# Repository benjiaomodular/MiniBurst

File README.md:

# MiniBurst
[![CC BY-SA 4.0][cc-by-sa-shield]][cc-by-sa]

## License

This work is licensed under a
[Creative Commons Attribution-ShareAlike 4.0 International License][cc-by-sa].

[![CC BY-SA 4.0][cc-by-sa-image]][cc-by-sa]

[cc-by-sa]: http://creativecommons.org/licenses/by-sa/4.0/
[cc-by-sa-image]: https://licensebuttons.net/l/by-sa/4.0/88x31.png
[cc-by-sa-shield]: https://img.shields.io/badge/License-CC%20BY--SA%204.0-lightgrey.svg

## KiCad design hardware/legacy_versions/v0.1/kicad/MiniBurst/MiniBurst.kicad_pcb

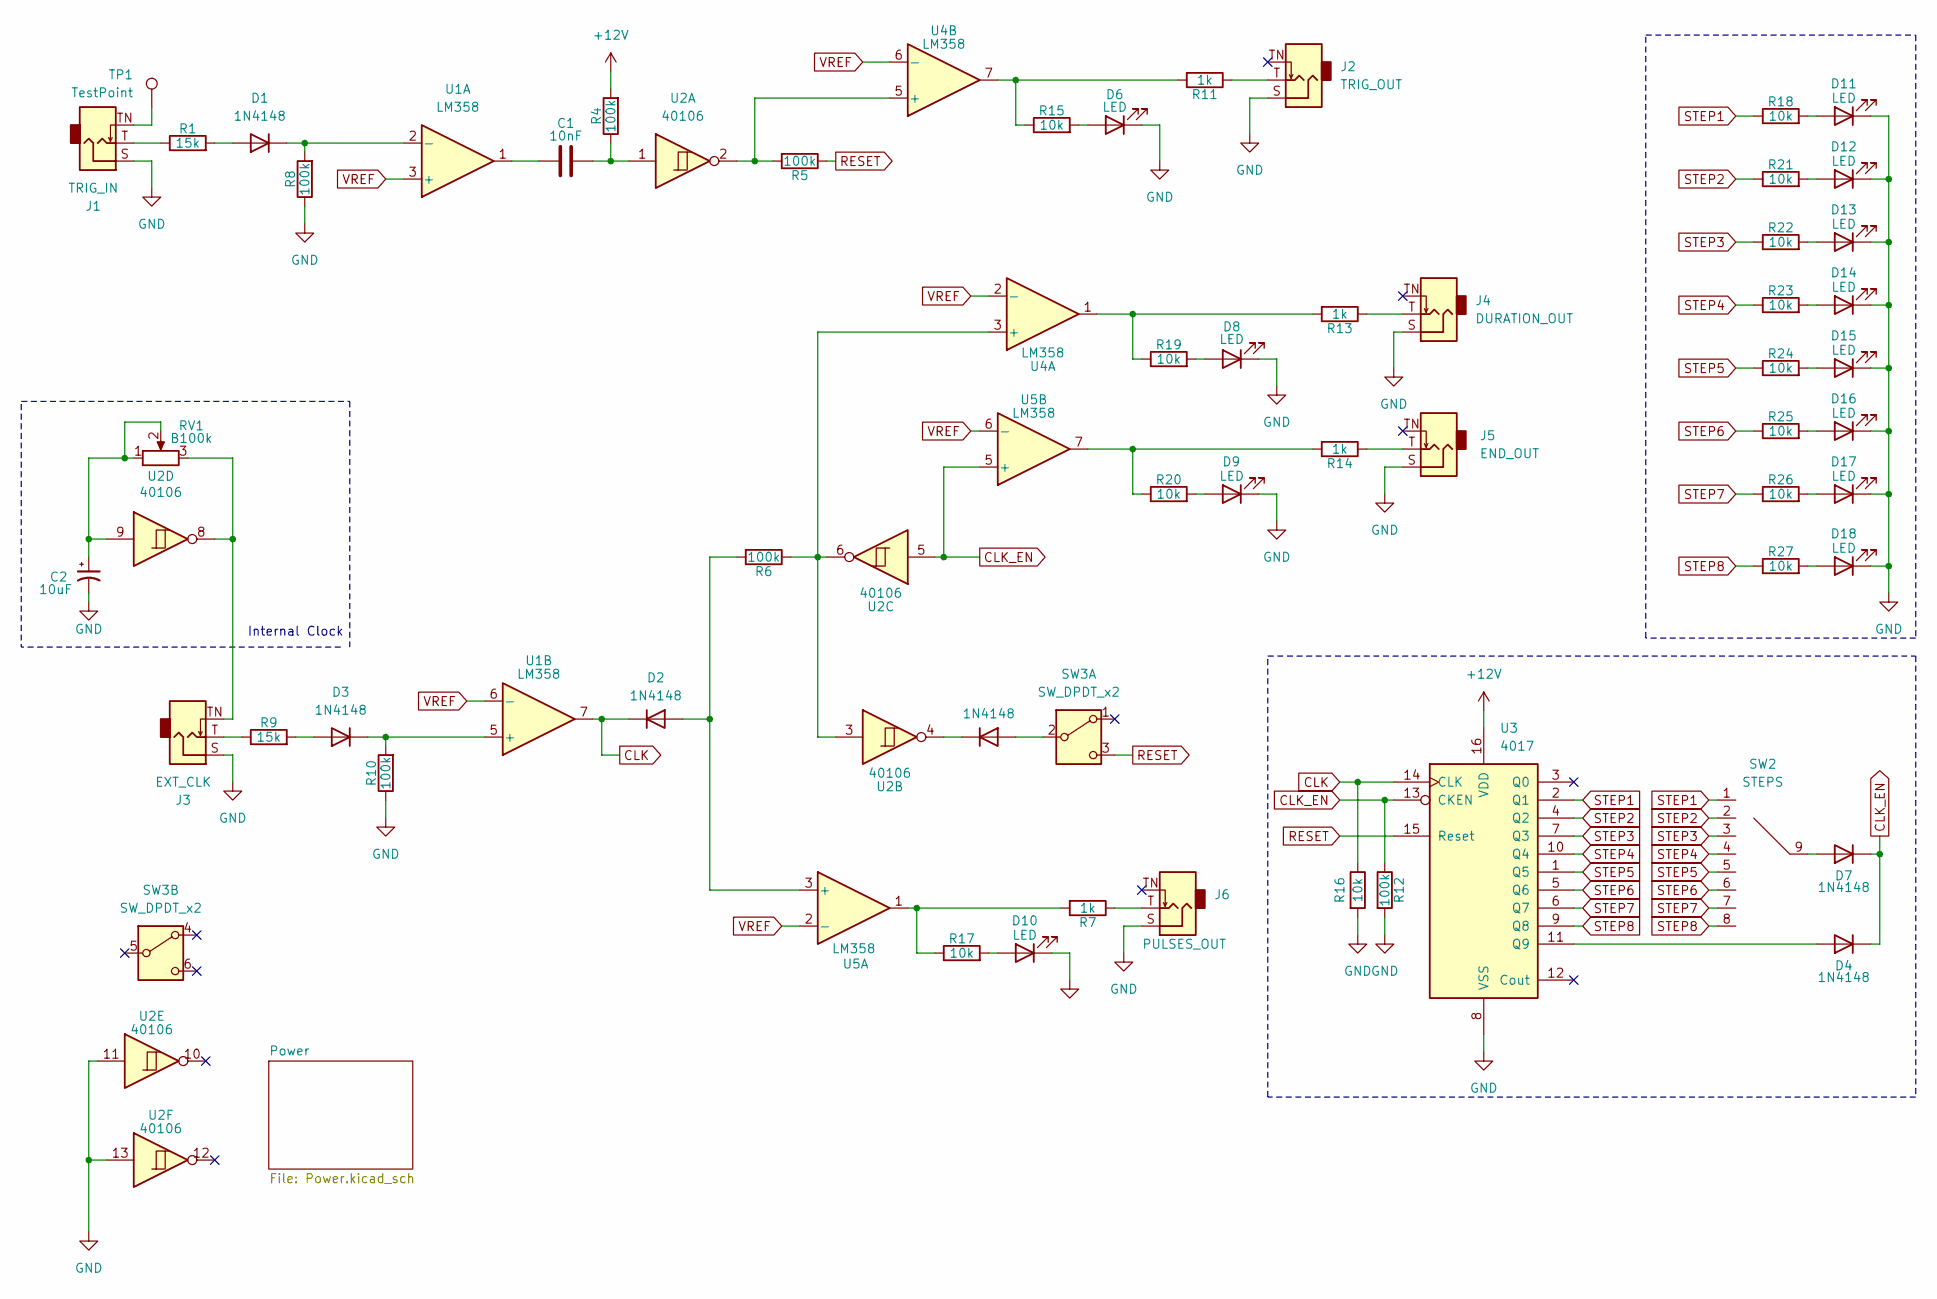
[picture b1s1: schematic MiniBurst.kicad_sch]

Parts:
C1: 10nF; C_0805_2012Metric_Pad1.18x1.45mm_HandSolder
C2: 10uF; C_0805_2012Metric_Pad1.18x1.45mm_HandSolder; Manufacturers Part Numb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 TMK212BBJ106KG8T
D1, D2, D3, D4, D5, D7: 1N4148; D_SOD-123
D6, D8, D9, D10, D11, D12, D13, D14, D15, D16, D17, D18: LED; LED_D3.0mm
J1: TRIG_IN; AudioJack_3.5mm
J2: TRIG_OUT; AudioJack_3.5mm
J3: EXT_CLK; AudioJack_3.5mm
J4: DURATION_OUT; AudioJack_3.5mm
J5: END_OUT; AudioJack_3.5mm
J6: PULSES_OUT; AudioJack_3.5mm
R1, R9: 15k; R_0805_2012Metric
R4, R5, R6, R8, R10, R12: 100k; R_0805_2012Metric
R7, R11, R13, R14: 1k; R_0805_2012Metric
R15, R16, R17, R18, R19, R20, R21, R22, R23, R24, R25, R26, R27: 10k; R_0805_2012Metric
RV1: B100k; Potentiometer_RV09; Manufacturers Part Numb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 RD901F-40-15R1-B100K
SW2: STEPS; RotarySwitch_SR16_POLE1_WAY8
SW3: SW_DPDT_x2; Button_KFC7x7
TP1: TestPoint; SolderWirePad_1x01_SMD_1x2mm
U1, U4, U5: LM358; SOIC-8_3.9x4.9mm_P1.27mm
U2: 40106; SOIC-14_3.9x8.7mm_P1.27mm
U3: 4017; SOIC-16_3.9x9.9mm_P1.27mm

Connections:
+12V: R4.2, U3.16 (VDD); also elsewhere on the board
CLK: D2.1 (K), R16.1, U1.7, U3.14 (CLK)
CLK_EN: D4.1 (K), D7.1 (K), R12.1, U2.5, U3.13 (CKEN), U5.5 (+)
GND: C2.2, D6.1 (K), D8.1 (K), D9.1 (K), D10.1 (K), D11.1 (K), D12.1 (K), D13.1 (K), D14.1 (K), D15.1 (K), D16.1 (K), D17.1 (K), D18.1 (K), J1.S, J2.S, J3.S, J4.S, J5.S, J6.S, R8.1, R10.1, R12.2, R16.2, U2.11, U2.13, U3.8 (VSS); also elsewhere on the board
unnamed: C1.1, U1.1
unnamed: C1.2, R4.1, U2.1
unnamed: C2.1, RV1.1, RV1.2, U2.9
unnamed: D1.2 (A), R1.2
unnamed: D1.1 (K), R8.2, U1.2 (-)
unnamed: D2.2 (A), R6.2, U5.3 (+)
unnamed: D3.2 (A), R9.2
unnamed: D3.1 (K), R10.2, U1.5 (+)
unnamed: D4.2 (A), U3.11 (Q9)
unnamed: D5.2 (A), SW3.2 (B)
unnamed: D5.1 (K), U2.4
unnamed: D6.2 (A), R15.2
unnamed: D7.2 (A), SW2.9
unnamed: D8.2 (A), R19.2
unnamed: D9.2 (A), R20.2
unnamed: D10.2 (A), R17.2
unnamed: D11.2 (A), R18.2
unnamed: D12.2 (A), R21.2
unnamed: D13.2 (A), R22.2
unnamed: D14.2 (A), R23.2
unnamed: D15.2 (A), R24.2
unnamed: D16.2 (A), R25.2
unnamed: D17.2 (A), R26.2
unnamed: D18.2 (A), R27.2
unnamed: J1.T, R1.1
unnamed: J1.TN, TP1.1
unnamed: J2.T, R11.1
unnamed: J3.T, R9.1
unnamed: J3.TN, RV1.3, U2.8
unnamed: J4.T, R13.1
unnamed: J5.T, R14.1
unnamed: J6.T, R7.1
unnamed: R11.2, R15.1, U4.7
unnamed: R13.2, R19.1, U4.1
unnamed: R14.2, R20.1, U5.7
unnamed: R7.2, R17.1, U5.1
unnamed: R6.1, U2.3, U2.6, U4.3 (+)
unnamed: R5.2, U2.2, U4.5 (+)
RESET: R5.1, SW3.3 (C), U3.15 (Reset)
STEP1: R18.1, SW2.1, U3.2 (Q1)
STEP2: R21.1, SW2.2, U3.4 (Q2)
STEP3: R22.1, SW2.3, U3.7 (Q3)
STEP4: R23.1, SW2.4, U3.10 (Q4)
STEP5: R24.1, SW2.5, U3.1 (Q5)
STEP6: R25.1, SW2.6, U3.5 (Q6)
STEP7: R26.1, SW2.7, U3.6 (Q7)
STEP8: R27.1, SW2.8, U3.9 (Q8)
VREF: U1.3 (+), U1.6 (-), U4.2 (-), U4.6 (-), U5.2 (-), U5.6 (-); also elsewhere on the board

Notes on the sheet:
Internal Clock

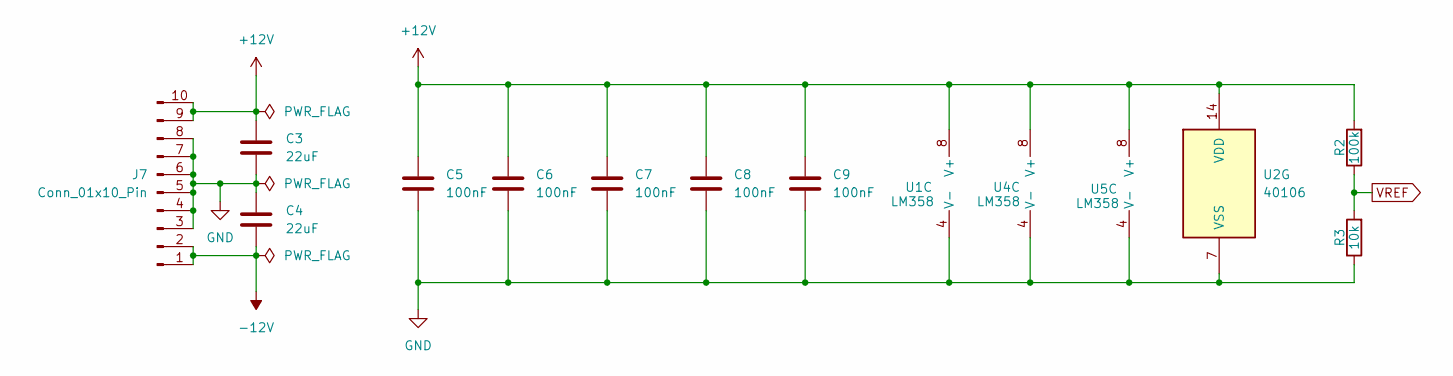
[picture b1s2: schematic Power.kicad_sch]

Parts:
C3, C4: 22uF; CP_Elec_6.3x4.5; Manufacturers Part Numb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 GRM21BR61E226ME44L
C5, C6, C7, C8, C9: 100nF; C_0805_2012Metric_Pad1.18x1.45mm_HandSolder
J7: Conn_01x10_Pin; Header_IDC2x05_NoArrow
R2: 100k; R_0805_2012Metric
R3: 10k; R_0805_2012Metric
U1, U4, U5: LM358; SOIC-8_3.9x4.9mm_P1.27mm
U2: 40106; SOIC-14_3.9x8.7mm_P1.27mm

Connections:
+12V: C3.1, C5.1, C6.1, C7.1, C8.1, C9.1, J7.9, J7.10, R2.2, U1.8 (V+), U2.14 (VDD), U4.8 (V+), U5.8 (V+); also elsewhere on the board
-12V: C4.2, J7.1, J7.2
GND: C3.2, C4.1, C5.2, C6.2, C7.2, C8.2, C9.2, J7.3, J7.4, J7.5, J7.6, J7.7, J7.8, R3.1, U1.4 (V-), U2.7 (VSS), U4.4 (V-), U5.4 (V-); also elsewhere on the board
VREF: R2.1, R3.2; also elsewhere on the board

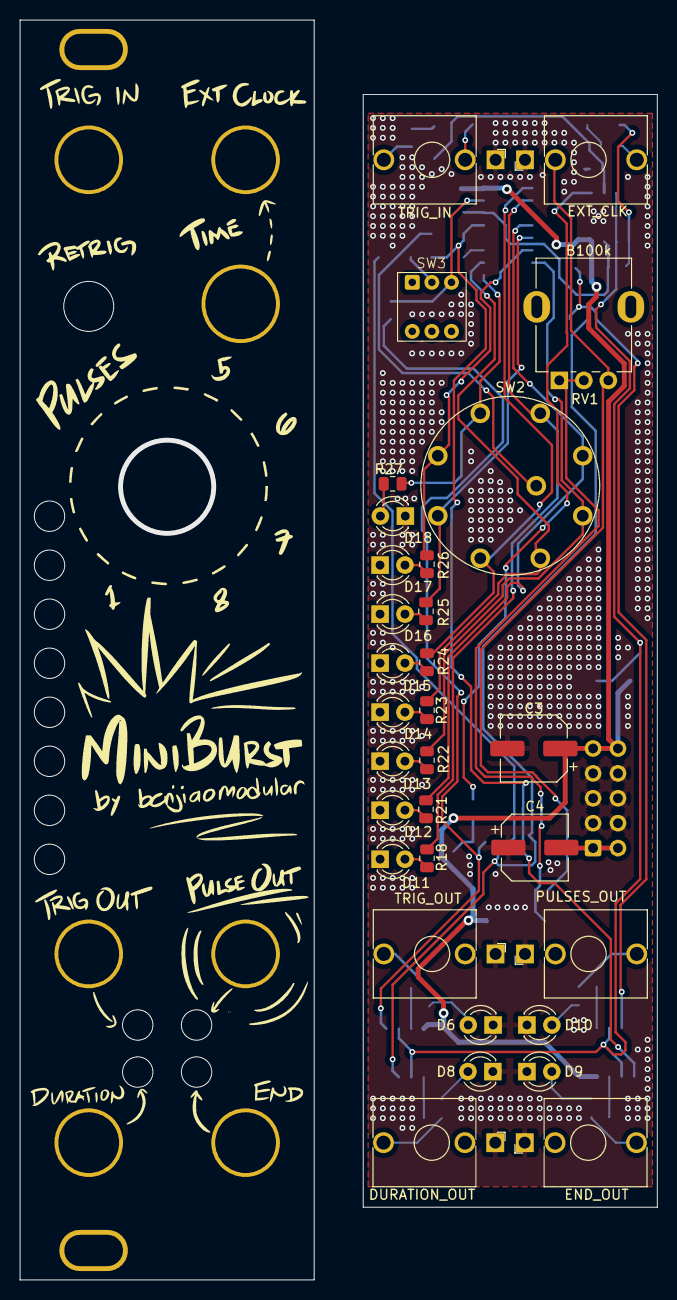
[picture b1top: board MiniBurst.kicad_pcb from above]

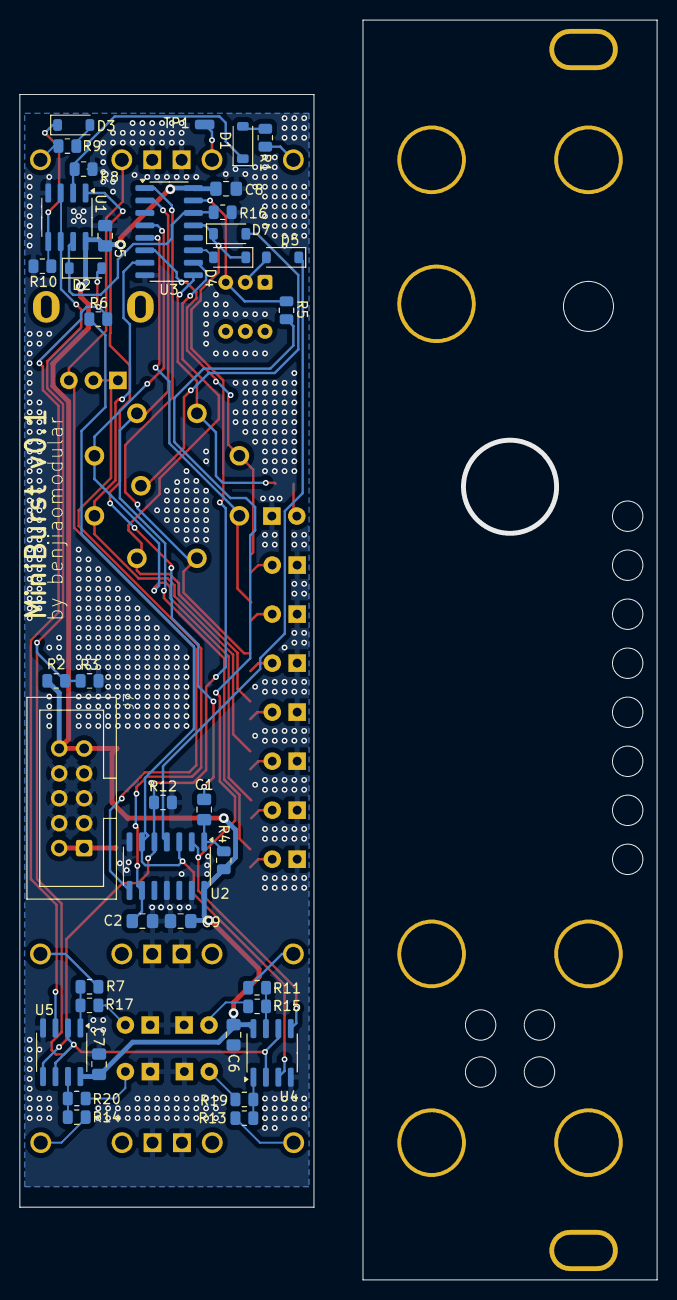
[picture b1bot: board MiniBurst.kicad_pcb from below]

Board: 2 copper layers, 30.0 x 113.5 mm, 70 parts (39 on the bottom side), 53 nets.

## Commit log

2024-09-06 Reorganized files
2024-09-07 done with panel art
2024-09-10 v0.1 PCB
2024-09-11 Added copper fill to panel
2024-10-27 Adjusted main pcb dimensions to fit 3d printed rails
2024-10-27 Added schem PDF
2024-10-28 Added schematics
